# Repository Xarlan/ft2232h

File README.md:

# ft2232h
USB to UART/SPI/I2C/JTAG

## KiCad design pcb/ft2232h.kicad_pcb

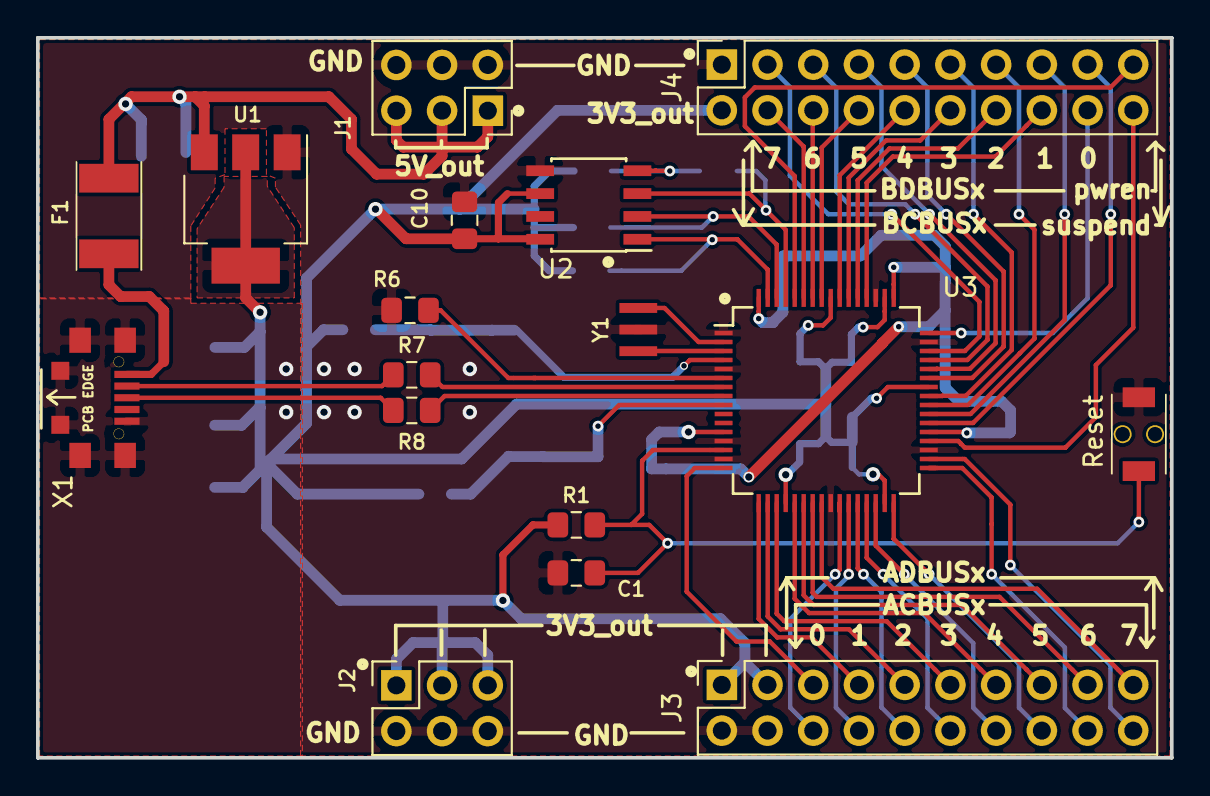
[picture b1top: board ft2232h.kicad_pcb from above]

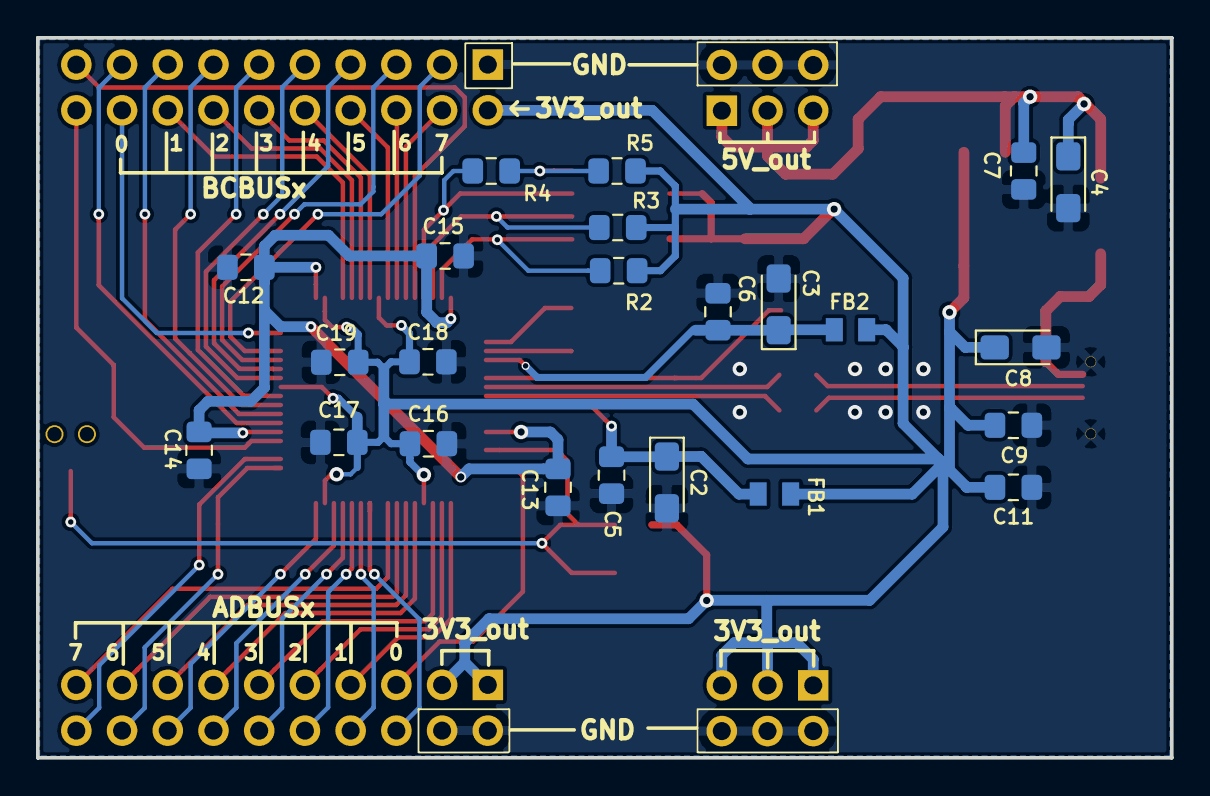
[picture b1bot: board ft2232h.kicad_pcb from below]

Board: 2 copper layers, 63.0 x 40.0 mm, 40 parts (23 on the bottom side), 53 nets.

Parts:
C1, C5, C6, C7, C9, C10, C11, C13, C14, C15, C16, C17, C18, C19: 0.1uF/50V; C_0805_2012Metric_Pad1.15x1.40mm_HandSolder
C2, C3, C4, C8: 4.7uF/10V; CP_EIA-3216-18_Kemet-A_Pad1.58x1.35mm_HandSolder
C12: 3.3uF; C_0805_2012Metric_Pad1.15x1.40mm_HandSolder
F1: F_Small; MF-MSMF050
FB1, FB2: FerriteB; FerriteBead
J1, J2: PBD-6; PinSocket_2x03_P2.54mm_Vertical
J3, J4: PBD-2x10; PinSocket_2x10_P2.54mm_Vertical
R1: 1kOhm; R_0805_2012Metric_Pad1.15x1.40mm_HandSolder
R2, R3, R5: 10kOhm; R_0805_2012Metric_Pad1.15x1.40mm_HandSolder
R4: 2kOhm; R_0805_2012Metric_Pad1.15x1.40mm_HandSolder
R6: 12kOhm; R_0805_2012Metric_Pad1.15x1.40mm_HandSolder
R7, R8: 10 Ohm; R_0805_2012Metric_Pad1.15x1.40mm_HandSolder
Reset: SW_PUSH_SMALL; IT-1185AP
U1: AMS1117; SOT-223
U2: eeprom_93C46; SOIC-8_3.9x4.9mm_P1.27mm
U3: FT2232H; LQFP-64_10x10mm_P0.5mm
X1: micro_USB; micro_USB_KLS1-233-0-0-1-T
Y1: 12MHz; CSTCE_G15C

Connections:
/1.8V: C12.1, C13.1, C14.1, C15.1, U3.12, U3.37, U3.49, U3.64
/3.3V: C8.1, C9.1, C10.1, C11.1, C16.1, C17.1, C18.1, C19.1, FB1.1, FB2.1, J2.1, J2.3, J2.5, J3.1, J3.3, J4.2, R1.1, R2.2, R3.2, R5.2, U1.2, U1.4, U2.6, U2.8, U3.20, U3.31, U3.42, U3.50, U3.56
/5V_out: C4.1, C7.1, F1.2, J1.1, J1.3, J1.5, U1.3
/ACBUS0: J3.6, U3.26
/ACBUS1: J3.8, U3.27
/ACBUS2: J3.10, U3.28
/ACBUS3: J3.12, U3.29
/ACBUS4: J3.14, U3.30
/ACBUS5: J3.16, U3.32
/ACBUS6: J3.18, U3.33
/ACBUS7: J3.20, U3.34
/ADBUS0: J3.5, U3.16
/ADBUS1: J3.7, U3.17
/ADBUS2: J3.9, U3.18
/ADBUS3: J3.11, U3.19
/ADBUS4: J3.13, U3.21
/ADBUS5: J3.15, U3.22
/ADBUS6: J3.17, U3.23
/ADBUS7: J3.19, U3.24
/BCBUS0: J4.18, U3.48
/BCBUS1: J4.16, U3.52
/BCBUS2: J4.14, U3.53
/BCBUS3: J4.12, U3.54
/BCBUS4: J4.10, U3.55
/BCBUS5: J4.8, U3.57
/BCBUS6: J4.6, U3.58
/BCBUS7: J4.4, U3.59
/BDBUS0: J4.17, U3.38
/BDBUS1: J4.15, U3.39
/BDBUS2: J4.13, U3.40
/BDBUS3: J4.11, U3.41
/BDBUS4: J4.9, U3.43
/BDBUS5: J4.7, U3.44
/BDBUS6: J4.5, U3.45
/BDBUS7: J4.3, U3.46
/CLK: R3.1, U2.2, U3.62
/CS: R2.1, U2.1, U3.63
/DM_N: R7.1, X1.2
/DP_P: R8.1, X1.3
/Data: R4.1, U2.3, U3.61
/VPHY: C3.1, C6.1, FB2.2, U3.4
/VPLL: C2.1, C5.1, FB1.2, U3.9
/osci: U3.2, Y1.1
/osco: U3.3, Y1.3
/pwren: J4.19, U3.60
/rst: C1.1, R1.2, Reset.2, U3.14
/suspend: J4.20, U3.36
Earth: C1.2, C2.2, C3.2, C4.2, C5.2, C6.2, C7.2, C8.2, C9.2, C10.2, C11.2, C12.2, C13.2, C14.2, C15.2, C16.2, C17.2, C18.2, C19.2, J1.2, J1.4, J1.6, J2.2, J2.4, J2.6, J3.2, J3.4, J4.1, R6.1, Reset.1, U1.1, U2.5, U3.1, U3.5, U3.10, U3.11, U3.13, U3.15, U3.25, U3.35, U3.47, U3.51, X1.0, X1.5, Y1.2
unnamed: F1.1, X1.1
unnamed: R4.2, R5.1, U2.4
unnamed: R6.2, U3.6
unnamed: R7.2, U3.7
unnamed: R8.2, U3.8

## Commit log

2018-10-26 redraw pcb
2018-10-28 plot GND, schematic to pdf
2018-10-29 update top/bottom picture
2018-12-21 Update README.md
    fix the typo.
    this typo was found by Denis Pekun
